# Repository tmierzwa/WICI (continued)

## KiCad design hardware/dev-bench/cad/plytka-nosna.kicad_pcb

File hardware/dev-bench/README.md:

# WICI: płytka v1 prototypu

Płytka v1 (dawniej płytka nośna N1) łączy kupione moduły w prototyp stacji na biurku: ESP32-S3-DevKitC-1 w gniazdach, moduł Seeed Wio SX1262 na przewodach obok płytki, panel Sharp LS027B7DH01A, pamięć FRAM z ochroną przy zaniku zasilania, przyciski, przełącznik CISZA, diodę alarmu i brzęczyk. Własnego toru RF ani zasilania z ogniw i 12 V nie ma; zasila ją USB. Prototyp jest sprzętem kroku 4 planu ([koncepcja, rozdział 08](../../docs/concept/08-plan-weryfikacji-i-decyzje.html#kolejnosc-prac)), a jego wnioski przechodzą do płytki v2 stacji pilotażowej ([elektronika](../../docs/spec/elektronika.md#stacja-pilotażowa)). Katalog i pliki zachowują dawne nazwy (`dev-bench`, `fabrication/N1`), bo wykonawca prototypu pracuje na tych ścieżkach.

## Wersje

| Wersja | Stan |
|---|---|
| v1 | 5 płytek z JLCPCB zamówionych 2026-10-10, w tym 2 z montażem SMD ([zamówienie](przed-produkcja.md#zamówienie-2026-10-10-l0)). Dwie zmontowane płytki są w montażu u wykonawcy jako prototypy ([zlecenie](../l0-diagnostic/ZLECENIE.md)); trzy są gołe. Panel nie mieści się na v1 w obrysie z opisu płytki (F118); sposób ułożenia podaje krok 7 [uruchomienia](uruchomienie.md#montaż). R12 wymienia się przy montażu na 1 kΩ |
| v1.1 | projekt na `main`: złącze panelu J7 odsunięte na zmierzoną długość taśmy FPC ([F118](../../docs/review.md)). Nie do zamówienia; jest bazą płytki v2. Wycenę pełnego montażu SMD i THT w JLCPCB sprawdzono w zamkniętym [PR #129](https://github.com/tmierzwa/WICI/pull/129) |

Pliki produkcyjne w `fabrication/N1/` są rewizji v1.1. Pliki zamówionej rewizji v1 wskazuje tag [`hw-dev-bench-v1`](https://github.com/tmierzwa/WICI/tree/hw-dev-bench-v1/hardware/dev-bench/fabrication/N1) (commit `e137e13`, SHA-256 paczki `wici-plytka-nosna-N1-gerber.zip`: `01598fff…ef11ac`). Samej paczki wysłanej do JLCPCB nie mamy, więc nie porównano jej z tagiem. Pliki produkcyjne i projekt nie zmieniały się jednak od tego commitu aż do przejścia na v1.1.

## Prototyp

Odbiór zmontowanego prototypu (radio, FRAM, ekran, wejścia, dioda, brzęczyk, wspólna magistrala SPI) robi program diagnostyczny ([l0-diagnostic](../l0-diagnostic/README.md)) według [instrukcji montażu i testów](../l0-diagnostic/MONTAZ-I-TESTY.md). Połączenia MCU prototypu są w [tabeli prototypu](../l0-diagnostic/reference/polaczenia-MCU-L0.csv). Po odbiorze na prototyp wgrywa się program stacji, środowisko `l0` w [firmware](../../firmware/README.md).

Płytka ma też gniazda na moduły TI, ST i Nordic (J1–J4, J9, J10, JP3) z czasów stanowisk deweloperskich A/B. Prototyp ich nie używa, a v2 ich nie dostanie. Opis stanowisk jest w [archiwum](../archiwum/stanowiska-a-b.md); obrazy `bench-*` w `firmware/` dotyczą tylko stanowisk.

## Pliki

| Plik | Zawartość |
|---|---|
| [płytka v1](plytka-nosna.md) | opis płytki: przypisanie sygnałów, mechanika, zasilanie, koszt i dostępność, źródła |
| [połączenia](polaczenia.md) | piny każdego złącza i elementu (z generatora) |
| [schemat](schemat.pdf) | schemat w PDF, eksport z `cad/` |
| `cad/` | projekt KiCad 10.0.6: schemat, PCB, reguły, lokalne biblioteki |
| `tools/` | generatory schematu i PCB, eksport, kontrole; edytowalnym źródłem jest `tools/design.py` |
| `checks/` | raporty ERC/DRC, [zapis odtworzenia](checks/odtworzenie.md), [przymiarka](checks/przymiarka.md), [zgodność z oprogramowaniem stanowisk](checks/zgodnosc-firmware.md) |
| [BOM](bom.csv) | części z MPN |
| [pliki produkcyjne](fabrication/N1/README.md) | Gerber, wiercenia, pozycje, rysunek montażowy, wydruk 1:1 |
| [uruchomienie](uruchomienie.md) | montaż, kontrola przed zasilaniem, kalibracja VTEST, ochrona FRAM, pomiar oscyloskopem, wzór zapisu sztuki |
| [obsługa](obsluga.md) | obsługa stanowisk A/B (archiwalna; zasady dla panelu, VTEST i pomiaru prądu dotyczą też prototypu) |
| [przed zamówieniem](przed-produkcja.md) | zamówienie v1, stan v1.1, warunki zamówienia i odtworzenie z generatorów |

Licencje według [LICENSE.md](../../LICENSE.md): projekt płytki i pliki produkcyjne CERN-OHL-P-2.0, skrypty MIT, dokumentacja CC-BY-4.0.

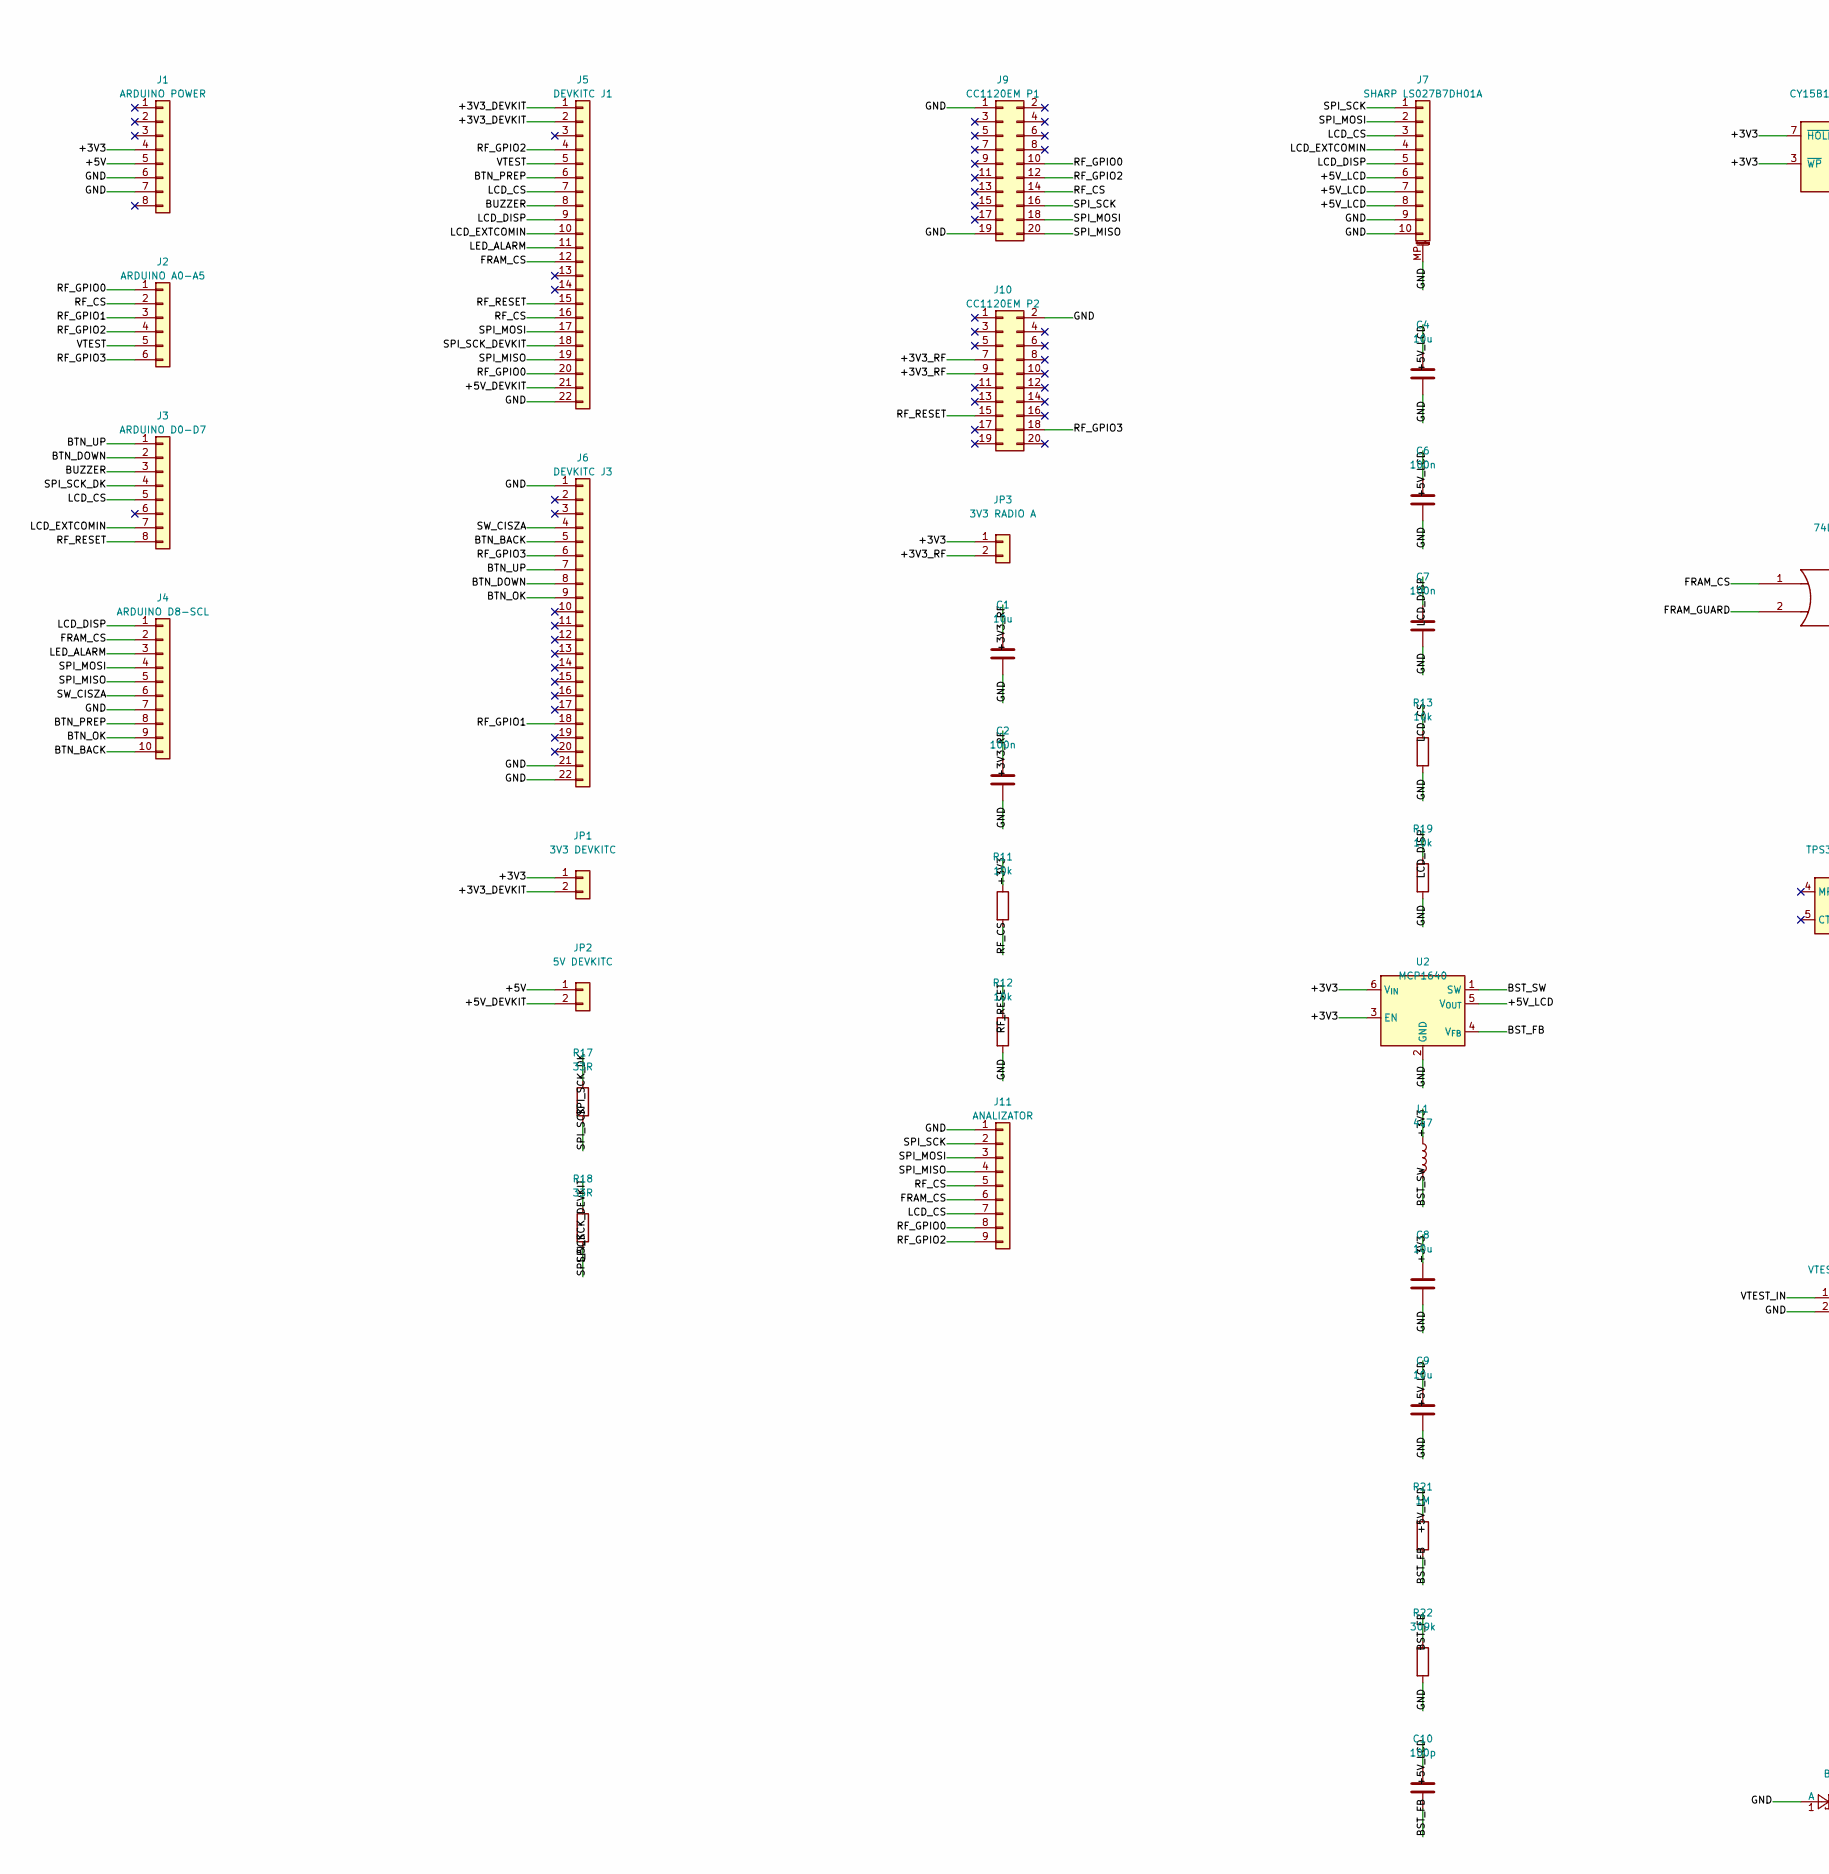
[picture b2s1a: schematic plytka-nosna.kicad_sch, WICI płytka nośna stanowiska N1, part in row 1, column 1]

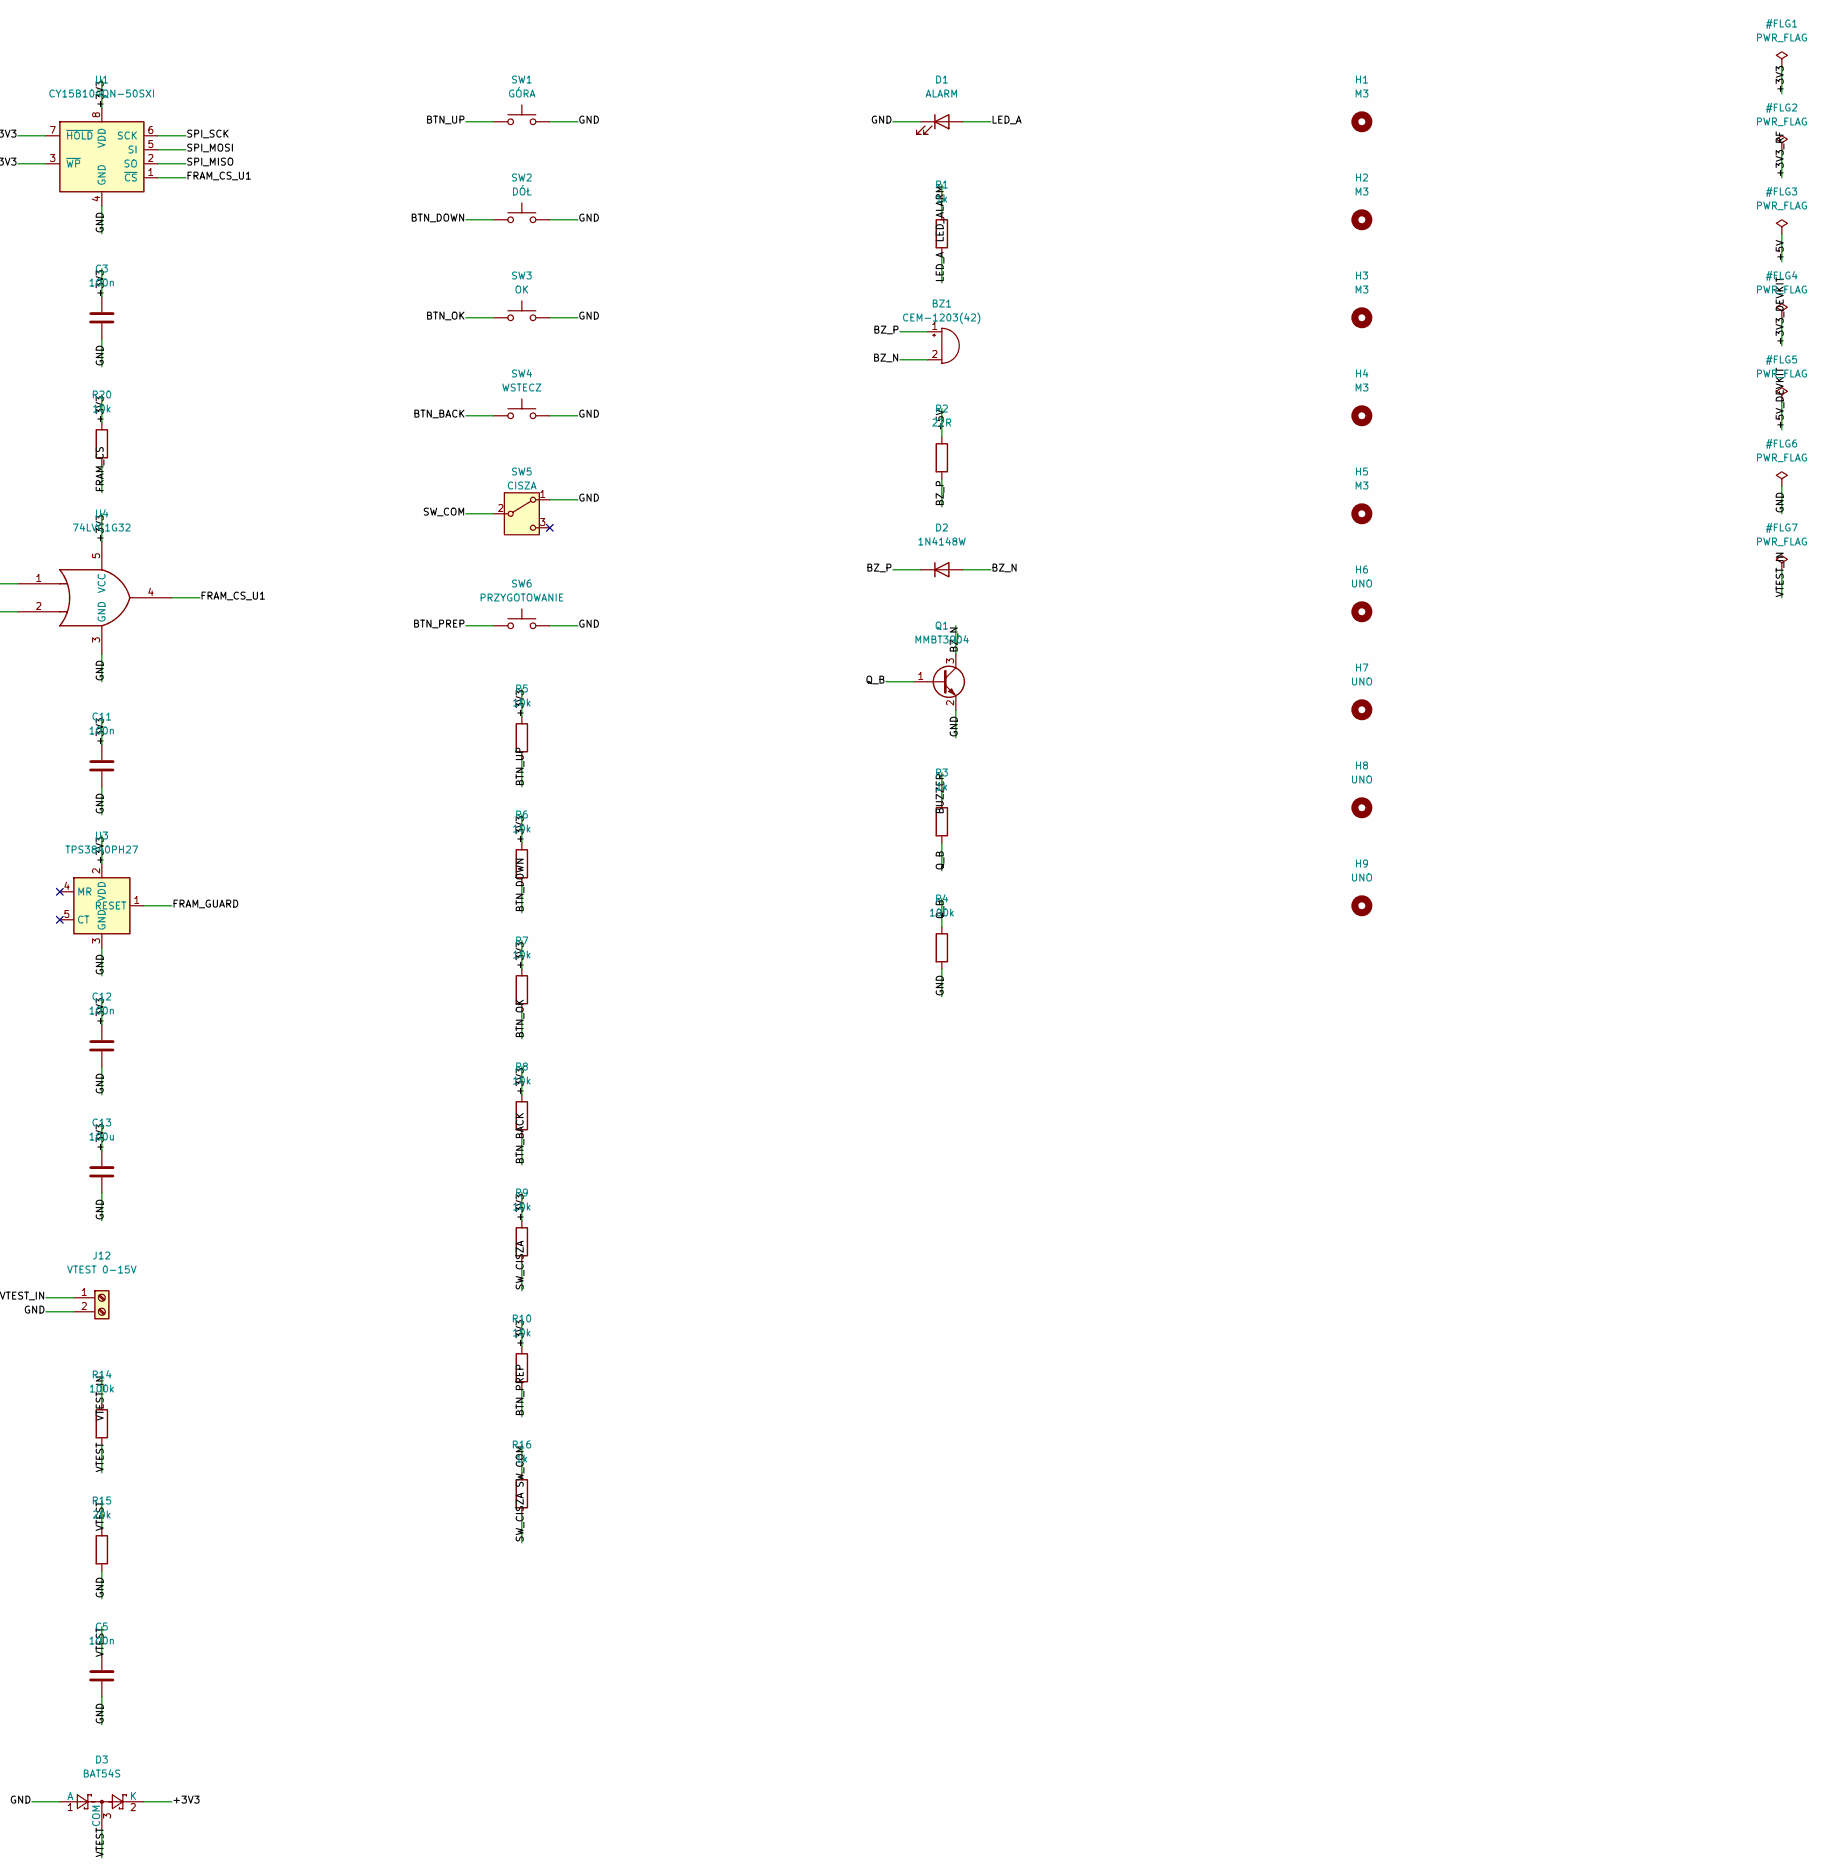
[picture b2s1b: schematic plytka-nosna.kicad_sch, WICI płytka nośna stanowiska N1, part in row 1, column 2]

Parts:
BZ1: CEM-1203(42); MagneticBuzzer_ProSignal_ABT-410-RC; MPN CEM-1203(42)
C1, C4, C8, C9: 10u; C_0805_2012Metric; MPN CL21A106KAYNNNG
C2, C3, C5, C6, C7, C11, C12: 100n; C_0805_2012Metric; MPN CL21B104KBCNNNC
C10: 100p; C_0805_2012Metric; MPN CL21C101JBANNNC
C13: 100u; C_1210_3225Metric; MPN LMK325ABJ107MM-P
D1: ALARM; LED_D5.0mm; MPN WP7113ID
D2: 1N4148W; D_SOD-123; MPN 1N4148W-7-F
D3: BAT54S; SOT-23; MPN BAT54SLT1G
H1, H2, H3, H4, H5: M3; MountingHole_3.2mm_M3
H6, H7, H8, H9: UNO; MountingHole_3.2mm_Arduino
J1: ARDUINO POWER; PinSocket_1x08_P2.54mm_Vertical; MPN SSQ-108-03-T-S
J2: ARDUINO A0-A5; PinSocket_1x06_P2.54mm_Vertical; MPN SSQ-106-03-T-S
J3: ARDUINO D0-D7; PinSocket_1x08_P2.54mm_Vertical; MPN SSQ-108-03-T-S
J4: ARDUINO D8-SCL; PinSocket_1x10_P2.54mm_Vertical; MPN SSQ-110-03-T-S
J5: DEVKITC J1; PinSocket_1x22_P2.54mm_Vertical; MPN PPTC221LFBN-RC
J6: DEVKITC J3; PinSocket_1x22_P2.54mm_Vertical; MPN PPTC221LFBN-RC
J7: SHARP LS027B7DH01A; Hirose_FH12-10S-0.5SH_1x10-1MP_P0.50mm_Horizontal; MPN FH12-10S-0.5SH(55)
J9: CC1120EM P1; PinHeader_2x10_P1.27mm_Vertical; MPN TFM-110-01-L-D
J10: CC1120EM P2; PinHeader_2x10_P1.27mm_Vertical; MPN TFM-110-01-L-D
J11: ANALIZATOR; PinHeader_1x09_P2.54mm_Vertical; MPN 61300911121
J12: VTEST 0-15V; TerminalBlock_Phoenix_MKDS-1,5-2-5.08_1x02_P5.08mm_Horizont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; MPN 1715721
JP1: 3V3 DEVKITC; PinHeader_1x02_P2.54mm_Vertical; MPN 61300211121
JP2: 5V DEVKITC; PinHeader_1x02_P2.54mm_Vertical; MPN 61300211121
JP3: 3V3 RADIO A; PinHeader_1x02_P2.54mm_Vertical; MPN 61300211121
L1: 4u7; L_Wuerth_WE-TPC-3816; MPN 744031004
Q1: MMBT3904; SOT-23; MPN MMBT3904LT1G
R1, R3, R16: 1k; R_0805_2012Metric; MPN RC0805FR-071KL
R2: 22R; R_1206_3216Metric; MPN RC1206FR-0722RL
R4: 100k; R_0805_2012Metric; MPN RC0805FR-07100KL
R5, R6, R7, R8, R9, R10, R11, R12, R13, R19, R20: 10k; R_0805_2012Metric; MPN RC0805FR-0710KL
R14: 100k; R_0805_2012Metric; MPN RT0805BRD07100KL
R15: 20k; R_0805_2012Metric; MPN RT0805BRD0720KL
R17, R18: 33R; R_0805_2012Metric; MPN RC0805FR-0733RL
R21: 1M; R_0805_2012Metric; MPN RC0805FR-071ML
R22: 309k; R_0805_2012Metric; MPN RC0805FR-07309KL
SW1: GÓRA; SW_SPST_Omron_B3F-40xx; MPN B3F-4055
SW2: DÓŁ; SW_SPST_Omron_B3F-40xx; MPN B3F-4055
SW3: OK; SW_SPST_Omron_B3F-40xx; MPN B3F-4055
SW4: WSTECZ; SW_SPST_Omron_B3F-40xx; MPN B3F-4055
SW5: CISZA; Toggle_ESwitch_100SP1T1B4M2QE; MPN 100SP1T1B4M2QE
SW6: PRZYGOTOWANIE; SW_TH_Tactile_Omron_B3F-100x; MPN B3F-1000
U1: CY15B104QN-50SXI; SOIC-8_5.3x5.3mm_P1.27mm; MPN CY15B104QN-50SXI
U2: MCP1640; SOT-23-6; MPN MCP1640T-I/CHY
U3: TPS3840PH27; SOT-23-5; MPN TPS3840PH27DBVR
U4: 74LVC1G32; SOT-23-5; MPN SN74LVC1G32DBVR

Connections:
/+3V3: C3.1, C8.1, C11.1, C12.1, C13.1, D3.2 (K), J1.4, JP1.1, JP3.1, L1.1, R5.1, R6.1, R7.1, R8.1, R9.1, R10.1, R11.1, R20.1, U1.3 (~WP), U1.7 (~HOLD), U1.8 (VDD), U2.3 (EN), U2.6 (V_{IN}), U3.2 (VDD), U4.5 (VCC)
/+3V3_DEVKIT: J5.1, J5.2, JP1.2
/+3V3_RF: C1.1, C2.1, J10.7, J10.9, JP3.2
/+5V: J1.5, JP2.1, R2.1
/+5V_DEVKIT: J5.21, JP2.2
/+5V_LCD: C4.1, C6.1, C9.1, C10.1, J7.6, J7.7, J7.8, R21.1, U2.5 (V_{OUT})
/BST_FB: C10.2, R21.2, R22.1, U2.4 (V_{FB})
/BST_SW: L1.2, U2.1 (SW)
/BTN_BACK: J4.10, J6.5, R8.2, SW4.1
/BTN_DOWN: J3.2, J6.8, R6.2, SW2.1
/BTN_OK: J4.9, J6.9, R7.2, SW3.1
/BTN_PREP: J4.8, J5.6, R10.2, SW6.1
/BTN_UP: J3.1, J6.7, R5.2, SW1.1
/BUZZER: J3.3, J5.8, R3.1
/BZ_N: BZ1.2 (-), D2.2 (A), Q1.3 (C)
/BZ_P: BZ1.1 (+), D2.1 (K), R2.2
/FRAM_CS: J4.2, J5.12, J11.6, R20.2, U4.1
/FRAM_CS_U1: U1.1 (~CS), U4.4
/FRAM_GUARD: U3.1 (RESET), U4.2
/GND: C1.2, C2.2, C3.2, C4.2, C5.2, C6.2, C7.2, C8.2, C9.2, C11.2, C12.2, C13.2, D1.1 (K), D3.1 (A), J1.6, J1.7, J4.7, J5.22, J6.1, J6.21, J6.22, J7.9, J7.10, J7.MP (MountPin), J9.1, J9.19, J10.2, J11.1, J12.2, Q1.2 (E), R4.2, R12.2, R13.2, R15.2, R19.2, R22.2, SW1.2, SW2.2, SW3.2, SW4.2, SW5.1 (A), SW6.2, U1.4 (GND), U2.2 (GND), U3.3 (GND), U4.3 (GND)
/LCD_CS: J3.5, J5.7, J7.3, J11.7, R13.1
/LCD_DISP: C7.1, J4.1, J5.9, J7.5, R19.1
/LCD_EXTCOMIN: J3.7, J5.10, J7.4
/LED_A: D1.2 (A), R1.2
/LED_ALARM: J4.3, J5.11, R1.1
/Q_B: Q1.1 (B), R3.2, R4.1
/RF_CS: J2.2, J5.16, J9.14, J11.5, R11.2
/RF_GPIO0: J2.1, J5.20, J9.10, J11.8
/RF_GPIO1: J2.3, J6.18
/RF_GPIO2: J2.4, J5.4, J9.12, J11.9
/RF_GPIO3: J2.6, J6.6, J10.18
/RF_RESET: J3.8, J5.15, J10.15, R12.1
/SPI_MISO: J4.5, J5.19, J9.20, J11.4, U1.2 (SO)
/SPI_MOSI: J4.4, J5.17, J7.2, J9.18, J11.3, U1.5 (SI)
/SPI_SCK: J7.1, J9.16, J11.2, R17.2, R18.2, U1.6 (SCK)
/SPI_SCK_DEVKIT: J5.18, R18.1
/SPI_SCK_DK: J3.4, R17.1
/SW_CISZA: J4.6, J6.4, R9.2, R16.2
/SW_COM: R16.1, SW5.2 (B)
/VTEST: C5.1, D3.3 (COM), J2.5, J5.5, R14.2, R15.1
/VTEST_IN: J12.1, R14.1

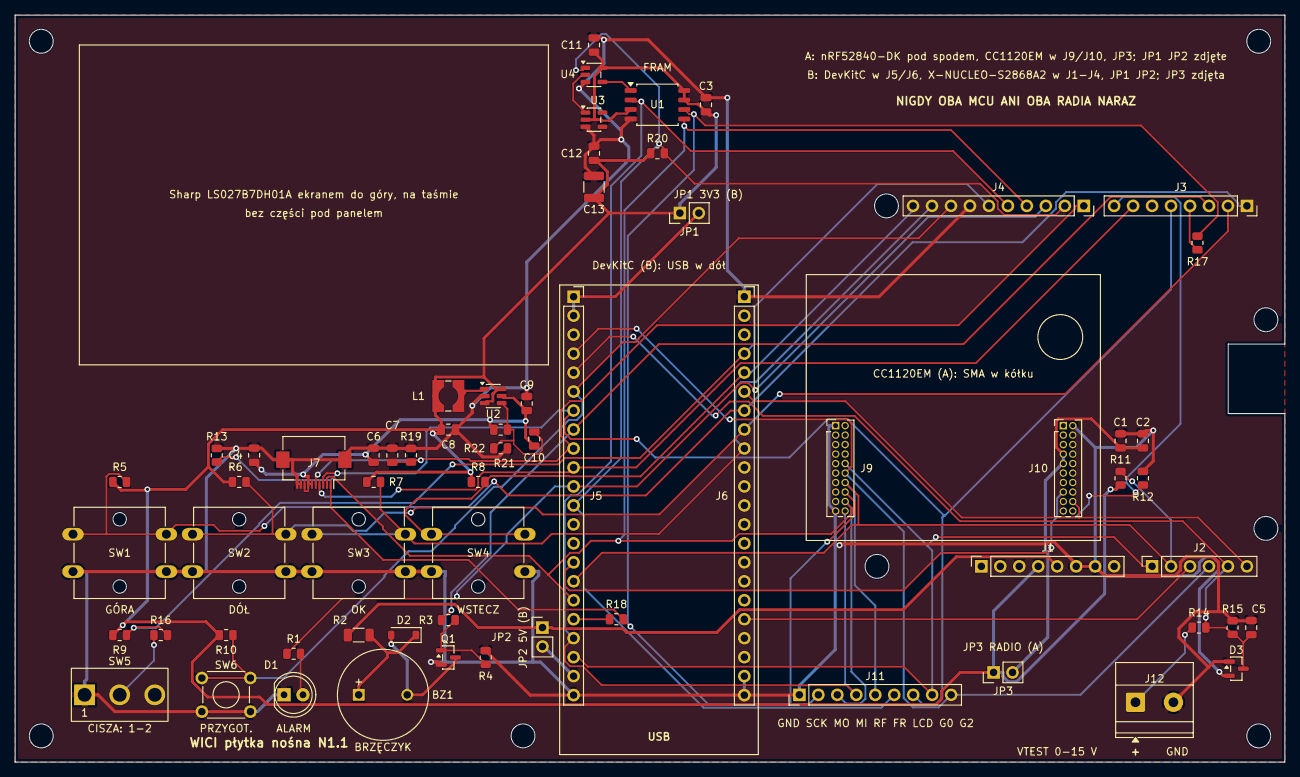
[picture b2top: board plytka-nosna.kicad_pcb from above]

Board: 2 copper layers, 170.0 x 100.0 mm, 74 parts (0 on the bottom side), 41 nets.

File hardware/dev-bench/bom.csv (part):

oznaczenia,ilość,wartość,producent,MPN,specyfikacja,footprint,stanowisko,uwagi
J1 J3,2,ARDUINO POWER / ARDUINO D0-D7,Samtec,SSQ-108-03-T-S,"gniazdo 1x8, 2,54 mm, przelotowe z długimi wyprowadzeniami 10,0 mm (stacking), cyna",Connector_PinSocket_2.54mm:PinSocket_1x08_P2.54mm_Vertical,A i B,wyprowadzenia od spodu wchodzą w gniazda Arduino nRF52840-DK
J2,1,ARDUINO A0-A5,Samtec,SSQ-106-03-T-S,"gniazdo 1x6, 2,54 mm, przelotowe z długimi wyprowadzeniami 10,0 mm (stacking), cyna",Connector_PinSocket_2.54mm:PinSocket_1x06_P2.54mm_Vertical,A i B,wyprowadzenia od spodu wchodzą w gniazda Arduino nRF52840-DK
J4,1,ARDUINO D8-SCL,Samtec,SSQ-110-03-T-S,"gniazdo 1x10, 2,54 mm, przelotowe z długimi wyprowadzeniami 10,0 mm (stacking), cyna",Connector_PinSocket_2.54mm:PinSocket_1x10_P2.54mm_Vertical,A i B,wyprowadzenia od spodu wchodzą w gniazda Arduino nRF52840-DK
J9 J10,2,CC1120EM P1 / CC1120EM P2,Samtec,TFM-110-01-L-D,"listwa Tiger Eye 2x10, 1,27 mm, przewlekana (styl -01), partner gniazd SFM-110-02-S-D-A modułu według karty Samtec F-226 (wysokość po złączeniu z SFM-02 do pomiaru)",Connector_PinHeader_1.27mm:PinHeader_2x10_P1.27mm_Vertical,A,moduł CC1120EM-868-915 wpina się od góry; pin 1 od strony SMA modułu
J5 J6,2,DEVKITC J1 / DEVKITC J3,Sullins,PPTC221LFBN-RC,"gniazdo żeńskie 1x22, 2,54 mm, proste, THT",Connector_PinSocket_2.54mm:PinSocket_1x22_P2.54mm_Vertical,B,ESP32-S3-DevKitC-1 wpina się od góry; pin 1 od strony anteny
J7,1,SHARP LS027B7DH01A,Hirose,FH12-10S-0.5SH(55),"złącze FPC 10-pin, 0,5 mm, styki od dołu, FPC 0,3 mm, SMD",Connector_FFC-FPC:Hirose_FH12-10S-0.5SH_1x10-1MP_P0.50mm_Horizontal,A i B,"panel Sharp LS027B7DH01A ekranem do góry, taśma FPC płasko; styk 1 panelu (SCLK) na padzie 1 po prawej"
U1,1,CY15B104QN-50SXI,Infineon,CY15B104QN-50SXI,"FRAM 4 Mbit SPI, 1,8–3,6 V, SOIC-8 208 mil",Package_SO:SOIC-8_5.3x5.3mm_P1.27mm,A i B,"zamiennik na tym samym footprincie: RAMXEED MB85RS4MTPF-G-BCERE1; pin 7 (HOLD albo RESET) i WP na stałe do 3,3 V"
U3,1,TPS3840PH27,Texas Instruments,TPS3840PH27DBVR,"nadzorca napięcia, próg 2,7 V ±1,5%, histereza 75–125 mV, wyjście push-pull aktywne stanem wysokim, SOT-23-5",Package_TO_SOT_SMD:SOT-23-5,A i B,"RESET = H, gdy +3V3 < 2,66–2,74 V; MR (4) i CT (5) wolne: opóźnienie startu ≤350 µs bez kondensatora"
U4,1,74LVC1G32,Texas Instruments,SN74LVC1G32DBVR,"bramka OR 1-kanałowa, 1,65–5,5 V, SOT-23-5",Package_TO_SOT_SMD:SOT-23-5,A i B,CS FRAM = CS z MCU lub RESET z U3: przy spadku zasilania FRAM niewybrana niezależnie od MCU
J11,1,ANALIZATOR,Würth Elektronik,61300911121,"listwa męska 1x9, 2,54 mm, THT",Connector_PinHeader_2.54mm:PinHeader_1x09_P2.54mm_Vertical,A i B,analizator stanów logicznych (8 kanałów); pin 1 = GND
JP1 JP2 JP3,3,3V3 DEVKITC / 5V DEVKITC / 3V3 RADIO A,Würth Elektronik,61300211121,"listwa męska 1x2, 2,54 mm, ze zworką",Connector_PinHeader_2.54mm:PinHeader_1x02_P2.54mm_Vertical,A i B,"JP1: założona tylko w stanowisku B; pomiar prądu 3,3 V; JP2: założona tylko w stanowisku B; zasila brzęczyk, pomiar prądu 5 V; JP3: założona w stanowisku A (zasila CC1120EM); amperomierz zamiast zworki mierzy prąd radia (zakres ≥200 mA); poza obrysem X-NUCLEO, bo listwa ze zworką (8,9 mm) sięga spodu nakładki w stanowisku B"
J12,1,VTEST 0-15V,Phoenix Contact,1715721,"zacisk śrubowy 2-pin, 5,08 mm","TerminalBlock_Phoenix:TerminalBlock_Phoenix_MKDS-1,5-2-5.08_1x02_P5.08mm_Horizontal",A i B,napięcie z zasilacza laboratoryjnego do prób progów ogniw i 12 V; najwyżej 15 V
SW1 SW2 SW3 SW4,4,GÓRA / DÓŁ / OK / WSTECZ,Omron,B3F-4055,"przycisk 12x12 mm z wysuniętym popychaczem, nasadka Omron B32-1310",Button_Switch_THT:SW_SPST_Omron_B3F-40xx,A i B,"pady 1 wspólne (12,5 mm), pady 2 wspólne; zestyk między grupami 1 i 2"
SW5,1,CISZA,E-Switch,100SP1T1B4M2QE,"przełącznik dźwigienkowy SPDT ON-NONE-ON, wyprowadzenia PCB 4,70 mm",WICI:Toggle_ESwitch_100SP1T1B4M2QE,A i B,zwarte 1-2 = cisza radiowa (SW_CISZA = L); 2-3 = praca
SW6,1,PRZYGOTOWANIE,Omron,B3F-1000,przycisk 6x6 mm,Button_Switch_THT:SW_TH_Tactile_Omron_B3F-100x,A i B,na stacji pod plombowaną pokrywą
D1,1,ALARM,Kingbright,WP7113ID,"LED 5 mm czerwona, rozproszona",LED_THT:LED_D5.0mm,A i B,katoda (pad kwadratowy 1) do masy
R1 R3 R16,3,1k,Yageo,RC0805FR-071KL,1 kΩ 1% 0805,Resistor_SMD:R_0805_2012Metric,A i B,"R1: prąd diody około 1 mA; R3: rezystor bazy Q1; R16: SW_CISZA przez 1 kΩ: wyjście MCU na tej linii nie zwiera się do masy (0,3 V przy ciszy)"
BZ1,1,CEM-1203(42),Same Sky (CUI Devices),CEM-1203(42),"brzęczyk magnetyczny 12 mm, sterowany z zewnątrz, 2048 Hz, cewka 42 Ω",Buzzer_Beeper:MagneticBuzzer_ProSignal_ABT-410-RC,A i B,"pad 1 = ""+""; sprawdzić znak ""+"" na obudowie przy montażu"
R2,1,22R,Yageo,RC1206FR-0722RL,"22 Ω 1% 1206, 0,25 W",Resistor_SMD:R_1206_3216Metric,A i B,"brzęczyk z +5V, nie z szyny radia; około 3,3 V szczytowo na cewce, najwyżej około 75 mA przy stałym stanie wysokim BUZZER"
D2,1,1N4148W,Diodes Incorporated,1N4148W-7-F,"dioda 75 V, SOD-123",Diode_SMD:D_SOD-123,A i B,dioda gasząca cewki brzęczyka
Q1,1,MMBT3904,onsemi,MMBT3904LT1G,"NPN 40 V 200 mA, SOT-23",Package_TO_SOT_SMD:SOT-23,A i B,klucz brzęczyka
R4,1,100k,Yageo,RC0805FR-07100KL,100 kΩ 1% 0805,Resistor_SMD:R_0805_2012Metric,A i B,"Q1 wyłączony, gdy MCU nie steruje linią BUZZER"
R17 R18,2,33R,Yageo,RC0805FR-0733RL,33 Ω 1% 0805,Resistor_SMD:R_0805_2012Metric,A i B,R17: szeregowy SCK przy złączu Arduino D3: łagodzi zbocza na rozgałęzionej sieci; R18: szeregowy SCK przy GPIO12 DevKitC
R19 R20 R5 R6 R7 R8 R9 R10 R11 R12 R13,11,10k,Yageo,RC0805FR-0710KL,10 kΩ 1% 0805,Resistor_SMD:R_0805_2012Metric,A i B,"R19: DISP = L do startu MCU: ekran biały, pamięć obrazu zachowana; R20: FRAM niewybrana przed startem MCU; R5: podciągnięcie wejścia; R6: podciągnięcie wejścia; R7: podciągnięcie wejścia; R8: podciągnięcie wejścia; R9: podciągnięcie wejścia; R10: podciągnięcie wejścia; R11: radio niewybrane przed startem MCU; R12: A: CC1120 w resecie do startu MCU; B: S2-LP włączony (SDN = L); R13: ściąga LCD_CS do masy; CS ekranu jest aktywny stanem wysokim"
D3,1,BAT54S,onsemi,BAT54SLT1G,"podwójna dioda Schottky 30 V, SOT-23",Package_TO_SOT_SMD:SOT-23,A i B,"ogranicza VTEST do zakresu -0,3...+3,6 V przy odwrotnej polaryzacji albo za wysokim napięciu J12"
R14,1,100k,Yageo,RT0805BRD07100KL,"100 kΩ 0,1% 25 ppm/K 0805",Resistor_SMD:R_0805_2012Metric,A i B,"górny rezystor dzielnika VTEST; 0,1%, bo dzielnik z rezystorów 1% sam dawał do ±1,7% błędu skali"
R15,1,20k,Yageo,RT0805BRD0720KL,"20 kΩ 0,1% 25 ppm/K 0805",Resistor_SMD:R_0805_2012Metric,A i B,"VTEST = VTEST_IN / 6 (±0,17% z tolerancji); 15 V daje 2,5 V"
C1 C4 C8 C9,4,10u,Samsung Electro-Mechanics,CL21A106KAYNNNG,10 µF 25 V X5R 0805,Capacitor_SMD:C_0805_2012Metric,A i B,"C1: +3V3_RF przy module CC1120EM; C4: VDD panelu (Sharp zaleca ≥1 µF); C8: wejście U2 (karta: ≥4,7 µF); C9: wyjście U2; razem z C4 przy panelu ≥10 µF także po spadku pojemności przy 5 V"
C2 C3 C11 C12 C6 C7 C5,7,100n,Samsung Electro-Mechanics,CL21B104KBCNNNC,100 nF 50 V X7R 0805,Capacitor_SMD:C_0805_2012Metric,A i B,"C2: +3V3_RF przy module CC1120EM; C3: +3V3 przy FRAM U1; C11: +3V3 przy bramce U4; C12: +3V3 przy nadzorcy U3; C6: VDDA panelu (Sharp zaleca ≥0,1 µF); C7: DISP panelu (Sharp zaleca 0,1 µF); C5: filtr wejścia ADC VTEST"
C13,1,100u,Taiyo Yuden,LMK325ABJ107MM-P,100 µF 10 V X5R 1210,Capacitor_SMD:C_1210_3225Metric,A i B,"podtrzymanie +3V3 przez czas reakcji nadzorcy U3 (budżet w plytka-nosna.md, „Zasilanie”)"
U2,1,MCP1640,Microchip,MCP1640T-I/CHY,"przetwornica podwyższająca synchroniczna 0,65–5,5 V, PFM, SOT-23-6",Package_TO_SOT_SMD:SOT-23-6,A i B,"5,1 V panelu z +3V3 (3,0 V w stanowisku A); EN na stałe do VIN"
L1,1,4u7,Würth Elektronik,744031004,"4,7 µH, Isat 0,9 A, 105 mΩ, ekranowana, 3,8 × 3,8 mm",Inductor_SMD:L_Wuerth_WE-TPC-3816,A i B,cewka z tabeli 5-2 karty MCP1640
R21,1,1M,Yageo,RC0805FR-071ML,"1,00 MΩ 1% 0805",Resistor_SMD:R_0805_2012Metric,A i B,RTOP dzielnika U2
R22,1,309k,Yageo,RC0805FR-07309KL,309 kΩ 1% 0805,Resistor_SMD:R_0805_2012Metric,A i B,RBOT dzielnika U2
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
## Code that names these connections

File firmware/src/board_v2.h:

// SPDX-License-Identifier: MIT
// Prototyp płytki v2: ESP32-S3-DevKitC-1-N8R8 v1.1 w J5/J6, moduł Seeed Wio-SX1262 w J8/J9, FRAM U1, panel
// ekranu Sharp w J7, panel obsługi i tor zasilania z ogniw AA i 12 V. Przypisanie według
// hardware/plytka-v2/polaczenia.md (tabela „Sygnały MCU”, generowana z hardware/plytka-v2/tools/design.py);
// tests/test_board_netlist.py sprawdza je z hardware/plytka-v2/checks/netlist.xml. Przypisania v1.1 (L0)
// zostają, więc piny radia, FRAM, ekranu i panelu są takie jak w board_l0.h. Nowe są pomiar ogniw i 12 V,
// klucz dzielnika ogniw, PWM przetwornicy, INT i KILL sterownika wyłącznika oraz wykrywanie laptopa.
// Numery pinów to numery GPIO ESP32-S3.
#pragma once

#include <Arduino.h>

#include "mcu_sleep.h"

// Panel obsługi, linia DISP ekranu i pomiar na GPIO5 są jak na płytce nośnej N1 (board.h), więc v2 korzysta
// z tych samych ścieżek programu.
#define WICI_BOARD_N1 1
#define WICI_MCU_SLEEP 1  // lekkie uśpienie: listy SLEEP_HOLD i SLEEP_WAKE niżej, polecenie NAP
// Pętla czuwania (standby.h): uśpienie między terminami w zwykłej pracy. Wymaga wykrywania napięcia na VBUS
// (USB_LAPTOP) dla zasady 10 s, więc jest tylko na v2; L0 i XIAO śpią wyłącznie w poleceniu NAP.
#define WICI_STANDBY 1

namespace board {

constexpr const char* NAME = "v2";

// SPI: piny IO_MUX FSPI na kontrolerze SPI2, SCK przez 33 Ω (R18).
constexpr uint8_t SPI_SCK = 12;   // J5.18 -> R18 -> SPI_SCK; Wio J9.6
constexpr uint8_t SPI_MOSI = 11;  // J5.17; Wio J9.4
constexpr uint8_t SPI_MISO = 13;  // J5.19; Wio J9.5
constexpr uint8_t SPI_DRIVE = 0;  // gpio_drive_cap_t: 0 = najsłabszy

// SX1262 na Wio-SX1262.
constexpr uint8_t RADIO_CS = 10;    // J5.16 RF_CS -> Wio J8.4 NSS, aktywny stanem niskim; R11 10 kΩ do 3,3 V
constexpr uint8_t RADIO_RESET = 9;  // J5.15 RF_RESET -> Wio J8.3; R12 1 kΩ do masy: napędzany wysoko
constexpr uint8_t RADIO_BUSY = 14;  // J5.20 RF_GPIO0 -> Wio J8.2 BUSY, wejście
constexpr uint8_t RADIO_DIO1 = 21;  // J6.18 RF_GPIO1 -> Wio J8.1 DIO1, wejście przerwania
constexpr uint8_t RADIO_RXEN = 42;  // J6.6 RF_GPIO3 -> Wio J8.5 RXEN: wysoki w RX; R64 10 kΩ do masy

// FRAM U1 (przez bramkę U4 nadzorcy U3) na tej samej magistrali SPI.
constexpr uint8_t FRAM_CS = 8;  // J5.12; R20 10 kΩ do 3,3 V

// Panel Sharp w J7: SCS aktywny stanem wysokim (R13 10 kΩ do masy), EXTCOMIN z MCPWM, DISP wysoki po
// wyczyszczeniu ekranu (R19 10 kΩ do masy).
constexpr uint8_t DISPLAY_CS = 7;         // J5.7
constexpr uint8_t DISPLAY_EXTCOMIN = 17;  // J5.10
constexpr uint8_t DISPLAY_DISP = 16;      // J5.9
constexpr uint32_t DISPLAY_SPI_HZ = 1000000;

// Panel: przyciski do masy przez filtr RC (R80-R83, C60-C63), podciągnięte 10 kΩ do 3,3 V (R5-R8);
// przełącznik CISZA przez R16 1 kΩ, podciągnięty R9 10 kΩ.
constexpr uint8_t BTN_UP = 41;      // J6.7
constexpr uint8_t BTN_DOWN = 40;    // J6.8
constexpr uint8_t BTN_OK = 39;      // J6.9
constexpr uint8_t BTN_BACK = 2;     // J6.5
constexpr uint8_t SW_SILENCE = 1;   // J6.4; masa = cisza
constexpr uint8_t BTN_PREP = 6;     // J5.6; przycisk trybu przygotowania (R10 10 kΩ do 3,3 V)

// Dioda alarmu (aktywna stanem wysokim, R1 1 kΩ) i brzęczyk przez klucz Q1 (MMBT3904, R3 1 kΩ do bazy,
// R4 100 kΩ do masy): stan wysoki włącza brzęczyk, więc tylko przebieg z tone(), a w spoczynku stan niski.
constexpr uint8_t LED_ALARM = 18;  // J5.11
constexpr uint8_t BUZZER = 15;     // J5.8
constexpr uint16_t BUZZER_HZ = 2048;

// Pomiar 12 V (V_12_ADC) na GPIO5 (ADC1_CH4), tym samym pinie co VTEST na N1, więc polecenie VTEST podaje
// napięcie 12 V. Dzielnik to dzielnik UV sterownika U5: V12 -> R37 221 kΩ -> R38 10,0 kΩ -> węzeł V_12_DIV
// -> R39 15,4 kΩ -> masa (wszystkie 0,1%), czyli V_12_DIV = V12 × 15,4 / 246,4 = V12 / 16,00 (BOM: R39
// „0,0625 × V12”). R76 10 kΩ do pinu i C33 100 nF to filtr, nie część dzielnika. Napięcie jest tylko przy
// włączonej stacji (Q4 podłącza dzielnik z szyny ON); 36 V daje 2,25 V, w zakresie tłumienia 11 dB.
constexpr uint8_t VTEST = 5;  // J5.5
constexpr uint8_t VTEST_ADC_CHANNEL = 4;
constexpr uint8_t VTEST_DIVIDER = 16;

// Pomiar ogniw (V_AA_ADC) na GPIO4 (ADC1_CH3) przez klucz Q6 (DIV_EN wysoki podłącza dzielnik): R44 39,0 kΩ
// / R45 10,0 kΩ (0,1%), czyli V_AA = V_AA_DIV × 4,9. Program jeszcze go nie mierzy.
constexpr uint8_t BATTERY_ADC = 4;  // J5.4
constexpr uint8_t BATTERY_ADC_CHANNEL = 3;
constexpr uint8_t BATTERY_DIV_EN = 46;  // J5.14; pin konfiguracji startu, R43 100 kΩ do masy (niski przy resecie)

// Przetwornica 3,3 V (U7 LTC3115-1): PWM_SYNC wysoki = PWM na czas nadawania, niski = Burst Mode.
constexpr uint8_t CONVERTER_PWM = 45;  // J6.15; pin konfiguracji startu, R63 100 kΩ do masy (niski przy resecie)

// Sterownik wyłącznika U6 (LTC2955-2): INT to otwarty dren z R47 10 kΩ do 3,3 V, niski przy naciśniętym
// wyłączniku. KILL_MCU wysoki otwiera Q11, który ściąga KILL i wyłącza stację; R72 100 kΩ do masy trzyma Q11
// wyłączony przy resecie i bez sterowania.
constexpr uint8_t POWER_INT = 48;   // J6.16
constexpr uint8_t POWER_KILL = 47;  // J6.17

// Wykrywanie laptopa: VBUS gniazda USB-C przez R73/R74 włącza Q12, który ściąga USB_LAPTOP (R75 100 kΩ do
// 3,3 V): stan niski = napięcie na VBUS.
constexpr uint8_t USB_LAPTOP = 3;  // J5.13

// Diody stanu jak LED1-LED4 płytki DK: brak.
constexpr int16_t LED_HEARTBEAT = -1;
constexpr int16_t LED_RADIO = -1;
constexpr int16_t LED_FRAM = -1;
constexpr int16_t LED_USB = -1;

// Lekkie uśpienie (mcu_sleep.h, platform::sleep): wyjścia trzymane w uśpieniu przez gpio_hold_en, bo rezystory
// płytki ściągnęłyby je do stanu, który resetuje radio (R12 1 kΩ do masy na NRESET), wyłącza odbiór (RXEN do
// masy) albo wygasza ekran (DISP do masy); CS-y nieaktywne, a brzęczyk w stanie niskim.
// Na v2 dochodzą klucz dzielnika ogniw, tryb przetwornicy i KILL; program ich jeszcze nie steruje, więc hold
// zatrzaskuje stan z rezystorów do masy (R43, R63, R72: niski, stacja zostaje włączona).
constexpr uint8_t SLEEP_HOLD[] = {RADIO_CS, RADIO_RESET, RADIO_RXEN, FRAM_CS, DISPLAY_CS, DISPLAY_EXTCOMIN,
                                 DISPLAY_DISP, LED_ALARM, BUZZER, BATTERY_DIV_EN, CONVERTER_PWM, POWER_KILL};
// Linie budzenia: DIO1 stanem wysokim; przyciski, CISZA, INT wyłącznika i wykrywanie laptopa przy każdej zmianie
// stanu, bo INT trwa, dopóki wyłącznik jest wciśnięty, a USB_LAPTOP, dopóki jest napięcie na VBUS.
constexpr mcu_sleep::Line SLEEP_WAKE[] = {
    {RADIO_DIO1, mcu_sleep::Wake::ACTIVE_HIGH, "dio1"}, {BTN_UP, mcu_sleep::Wake::ANY_CHANGE, "up"},
    {BTN_DOWN, mcu_sleep::Wake::ANY_CHANGE, "down"},       {BTN_OK, mcu_sleep::Wake::ANY_CHANGE, "ok"},
    {BTN_BACK, mcu_sleep::Wake::ANY_CHANGE, "back"},       {SW_SILENCE, mcu_sleep::Wake::ANY_CHANGE, "silence"},
    {BTN_PREP, mcu_sleep::Wake::ANY_CHANGE, "prep"},       {POWER_INT, mcu_sleep::Wake::ANY_CHANGE, "power_int"},
    {USB_LAPTOP, mcu_sleep::Wake::ANY_CHANGE, "laptop"},
};

constexpr uint32_t SPI_HZ = 1000000;  // radio, jak na L0
constexpr uint32_t FRAM_SPI_HZ = 8000000;

}  // namespace board

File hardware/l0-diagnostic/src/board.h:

// SPDX-License-Identifier: MIT
#pragma once
#include <stdint.h>

namespace board {
constexpr uint8_t SPI_SCK = 12;
constexpr uint8_t SPI_MOSI = 11;
constexpr uint8_t SPI_MISO = 13;

constexpr uint8_t RADIO_NSS = 10;
constexpr uint8_t RADIO_NRST = 9;
constexpr uint8_t RADIO_BUSY = 14;
constexpr uint8_t RADIO_DIO1 = 21;
constexpr uint8_t RADIO_RXEN = 42;

constexpr uint8_t FRAM_CS = 8;
constexpr uint8_t LCD_CS = 7;
constexpr uint8_t LCD_EXTCOMIN = 17;
constexpr uint8_t LCD_DISP = 16;
constexpr uint8_t LED_ALARM = 18;
constexpr uint8_t BUZZER = 15;

constexpr uint8_t BTN_UP = 41;
constexpr uint8_t BTN_DOWN = 40;
constexpr uint8_t BTN_OK = 39;
constexpr uint8_t BTN_BACK = 2;
constexpr uint8_t SW_CISZA = 1;
constexpr uint8_t BTN_PREP = 6;
}  // namespace board

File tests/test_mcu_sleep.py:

# SPDX-License-Identifier: MIT
"""Wake levels of the light sleep (firmware/src/mcu_sleep.h) and the sleep lists of the L0 and v2 board files.

ESP32-S3 light sleep wakes on a level, not an edge. The harness models one sleep: a line wakes the MCU when its
level during the sleep equals the armed level. A held state (laptop connected, power switch pressed) must not wake
a second time; a change of level must (docs/spec/oprogramowanie.md, "Czuwanie")."""

from pathlib import Path
import sys
import unittest

sys.path.insert(0, str(Path(__file__).resolve().parent))
from test_radio_link_host import build_and_run, host_compiler, line  # noqa: E402  (stubs and host build)

HARNESS = r"""
#include <stdio.h>
#include "mcu_sleep.h"

using mcu_sleep::Line;
using mcu_sleep::Wake;

// Lines as on board v2: DIO1, one button, INT of the power switch and the laptop detection (both active low).
const Line LINES[] = {{21, Wake::ACTIVE_HIGH, "dio1"}, {39, Wake::ANY_CHANGE, "ok"},
                      {48, Wake::ANY_CHANGE, "power_int"}, {3, Wake::ANY_CHANGE, "laptop"}};
constexpr size_t N = 4;
uint8_t levels[N] = {0, 1, 1, 1};  // idle: DIO1 low, button released, switch released, no laptop

// One sleep: arm from the present levels, then the levels during the sleep are `during`. Returns the name of the
// waking line, "busy" when arming refused, "timer" when no line matched. Levels stay as `during` afterwards.
const char* nap(const uint8_t* during) {
    uint8_t armed[N] = {};
    if (mcu_sleep::arm(LINES, N, levels, armed) >= 0) return "busy";
    for (size_t i = 0; i < N; ++i) levels[i] = during[i];
    const int w = mcu_sleep::woke(N, levels, armed);
    return w >= 0 ? LINES[w].name : "timer";
}

int main() {
    const uint8_t idle[N] = {0, 1, 1, 1};
    const uint8_t laptop[N] = {0, 1, 1, 0};
    const uint8_t pressed[N] = {0, 1, 0, 1};
    const uint8_t button[N] = {0, 0, 1, 1};
    const uint8_t frame[N] = {1, 1, 1, 1};

    printf("IDLE %s\n", nap(idle));
    printf("PLUG %s\n", nap(laptop));            // laptop connected: wakes once
    // One nap() per statement: it changes `levels`, and GCC evaluates printf arguments right to left.
    const char* first = nap(laptop);
    const char* second = nap(laptop);
    printf("HELD %s %s\n", first, second);  // still connected: no second wake
    printf("UNPLUG %s\n", nap(idle));            // disconnected: change of level wakes
    printf("AFTER %s\n", nap(idle));
    printf("PRESS %s\n", nap(pressed));          // switch pressed: INT low
    printf("HOLD %s\n", nap(pressed));           // INT held low for the 5-19 s of a long press: no wake
    printf("RELEASE %s\n", nap(idle));
    const char* press = nap(button);
    const char* hold = nap(button);
    const char* release = nap(idle);
    printf("BUTTON %s %s %s\n", press, hold, release);
    const char* end = nap(frame);
    const char* pending = nap(frame);
    printf("FRAME %s %s\n", end, pending);  // DIO1 high wakes; while high there is no sleep
    levels[0] = 0;
    // Level back before the wake-up was read (contact bounce): no line named.
    uint8_t armed[N] = {};
    uint8_t now[N] = {0, 1, 1, 1};
    mcu_sleep::arm(LINES, N, now, armed);
    printf("BOUNCE %d\n", mcu_sleep::woke(N, now, armed));
    printf("CAUSES %s %s %s %s %s\n", mcu_sleep::causeName(mcu_sleep::Cause::TIMER), mcu_sleep::causeName(mcu_sleep::Cause::LINE),
           mcu_sleep::causeName(mcu_sleep::Cause::OTHER), mcu_sleep::causeName(mcu_sleep::Cause::REJECTED),
           mcu_sleep::causeName(mcu_sleep::Cause::BUSY));
    return 0;
}
"""

BOARD_HARNESS = r"""
#include <stdio.h>
#include BOARD

int main() {
    printf("HOLD");
    for (uint8_t pin : board::SLEEP_HOLD) printf(" %u", pin);
    printf("\nWAKE");
    for (const mcu_sleep::Line& l : board::SLEEP_WAKE)
        printf(" %s:%u:%s", l.name, l.pin, l.wake == mcu_sleep::Wake::ACTIVE_HIGH ? "high" : "change");
    printf("\n");
    return 0;
}
"""

L0_HOLD = "9 10 42 8 7 17 16 18 15"  # sorted below; radio CS, RESET, RXEN, FRAM CS, LCD CS, EXTCOMIN, DISP, LED, buzzer
L0_WAKE = ["dio1:21:high", "up:41:change", "down:40:change", "ok:39:change", "back:2:change", "silence:1:change",
           "prep:6:change"]


@unittest.skipUnless(host_compiler(), "no host C++ compiler")
class WakeLevelTests(unittest.TestCase):
    @classmethod
    def setUpClass(cls):
        cls.out = build_and_run(HARNESS, [])

    def test_no_line_change_ends_on_the_timer(self):
        self.assertEqual(line(self.out, "IDLE"), "IDLE timer")

    def test_laptop_wakes_on_connect_and_disconnect_but_not_while_connected(self):
        self.assertEqual(line(self.out, "PLUG"), "PLUG laptop")
        self.assertEqual(line(self.out, "HELD"), "HELD timer timer")
        self.assertEqual(line(self.out, "UNPLUG"), "UNPLUG laptop")
        self.assertEqual(line(self.out, "AFTER"), "AFTER timer")

    def test_power_switch_held_does_not_wake_again(self):
        self.assertEqual(line(self.out, "PRESS"), "PRESS power_int")
        self.assertEqual(line(self.out, "HOLD"), "HOLD timer")
        self.assertEqual(line(self.out, "RELEASE"), "RELEASE power_int")

    def test_button_press_hold_release(self):
        self.assertEqual(line(self.out, "BUTTON"), "BUTTON ok timer ok")

    def test_pending_radio_interrupt_blocks_sleep(self):
        self.assertEqual(line(self.out, "FRAME"), "FRAME dio1 busy")

    def test_bounce_names_no_line(self):
        self.assertEqual(line(self.out, "BOUNCE"), "BOUNCE -1")

    def test_cause_names(self):
        self.assertEqual(line(self.out, "CAUSES"), "CAUSES timer line other rejected busy")


@unittest.skipUnless(host_compiler(), "no host C++ compiler")
class BoardSleepListTests(unittest.TestCase):
    """The lists in board_l0.h and board_v2.h: outputs pulled by board resistors are held, lines that keep their
    state (switch INT, laptop detection, buttons) wake on a change and DIO1 on its high level."""

    def lists(self, header):
        out = build_and_run(BOARD_HARNESS, [], flags=[f'-DBOARD="{header}"'])
        return sorted(int(p) for p in line(out, "HOLD").split()[1:]), line(out, "WAKE").split()[1:]

    def test_l0(self):
        hold, wake = self.lists("board_l0.h")
        self.assertEqual(hold, sorted(int(p) for p in L0_HOLD.split()))
        self.assertEqual(wake, L0_WAKE)

    def test_v2_adds_divider_converter_kill_switch_and_laptop(self):
        hold, wake = self.lists("board_v2.h")
        # DIV_EN GPIO46, PWM_SYNC GPIO45, KILL_MCU GPIO47 (hardware/plytka-v2/polaczenia.md)
        self.assertEqual(hold, sorted([int(p) for p in L0_HOLD.split()] + [46, 45, 47]))
        # PWR_INT GPIO48, USB_LAPTOP GPIO3
        self.assertEqual(wake, L0_WAKE + ["power_int:48:change", "laptop:3:change"])


if __name__ == "__main__":
    unittest.main()
